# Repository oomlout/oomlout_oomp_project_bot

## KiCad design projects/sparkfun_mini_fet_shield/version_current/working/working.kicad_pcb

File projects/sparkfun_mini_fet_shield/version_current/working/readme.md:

# OOMP Project  
## Mini_FET_Shield  by sparkfun  
  
oomp key: oomp_projects_flat_sparkfun_mini_fet_shield  
(snippet of original readme)  
  
SparkFun Mini FET Shield  
========================================  

[*SparkFun Mini FET Shield (DEV-09627)*](https://www.sparkfun.com/products/9627)  
  
 Developed by Dave Vondle and IDEO Labs, this board is essentially the same as our Power Driver Shield, but the through-hole parts have been switched out for smaller SMD construction, allowing you to to drive high-current switches with your Arduino Pro Mini.   
 This is a great shield for small prototyping.  
  
 Repository Contents  
-------------------  
  
* **/Hardware** - Eagle design files (.brd, .sch)  
* **/Production** - Production panel files (.brd)  
  
Documentation  
--------------  
* **[Hookup Guide](https://learn.sparkfun.com/tutorials/mini-fet-shield-hookup-guide)** - Basic hookup guide for the Mini FET shield.  
* **[SparkFun Fritzing repo](https://github.com/sparkfun/Fritzing_Parts)** - Fritzing diagrams for SparkFun products.  
* **[SparkFun 3D Model repo](https://github.com/sparkfun/3D_Models)** - 3D models of SparkFun products.   

License Information  
-------------------  
This product is _**open source**_!   
  
The **hardware** is released under [Creative Commons ShareAlike 4.0 International](https://creativecommons.org/licenses/by-sa/4.0/).  
  
Please use, reuse, and modify these files as you see fit. Please maintain attribution to SparkFun Electronics and release anything derivative under the same license.  
  
Distributed as-is; no warranty is given.  
  
-   
  full source readme at [readme_src.md](readme_src.md)  
  
source repo at: [https://github.com/sparkfun/Mini_FET_Shield](https://github.com/sparkfun/Mini_FET_Shield)  
## Board  

## Schematic  

[schematic pdf](working_schematic.pdf)  
## Images

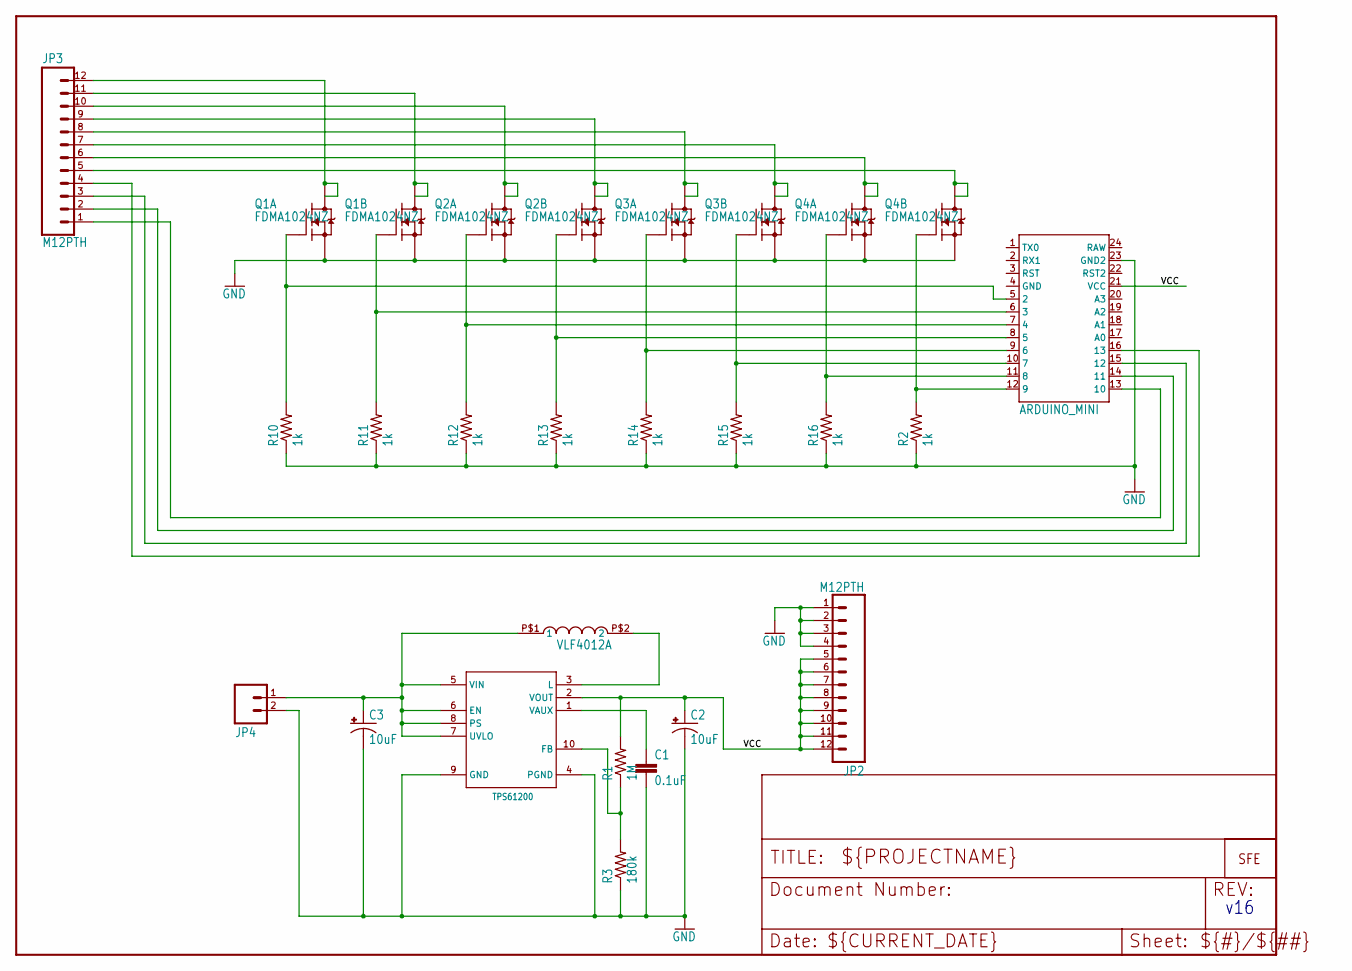
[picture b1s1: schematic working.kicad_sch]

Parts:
C1: 0.1uF; 0402-CAP
C2, C3: 10uF; EIA3216
JP2, JP3: M12PTH; 1X12
JP4: M02PTH; 1X02
JP5: LOGO-SFESK; SFE-LOGO-FLAME
Q1, Q2, Q3, Q4: FDMA1024NZ; MICROFET_2X2
R1: 1M; 0402-RES
R2, R10, R11, R12, R13, R14, R15, R16: 1k; 0402-RES
R3: 180k; 0402-RES
U1: TPS61200; DRC-S-PVSON-N10
U2: ARDUINO_MINI
UNK2.2UH0: VLF4012A

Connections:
GND: C1.2, C2.C (-), C3.C (-), JP2.1, JP2.2, JP2.3, JP2.4, JP4.2, Q1.S1 (S), Q1.S2 (S), Q2.S1 (S), Q2.S2 (S), Q3.S1 (S), Q3.S2 (S), Q4.S1 (S), Q4.S2 (S), R2.1, R3.1, R10.1, R11.1, R12.1, R13.1, R14.1, R15.1, R16.1, U1.4 (PGND), U1.9 (GND), U2.23 (GND2)
unnamed: JP3.4, U2.16 (13)
unnamed: R1.1, R3.2, U1.10 (FB)
unnamed: C1.1, U1.1 (VAUX)
unnamed: U1.3 (L), UNK2.2UH0.P$2 (2)
unnamed: Q1.G1 (G), R10.2, U2.5 (2)
unnamed: C3.A (+), JP4.1, U1.5 (VIN), U1.6 (EN), U1.7 (UVLO), U1.8 (PS), UNK2.2UH0.P$1 (1)
unnamed: Q1.G2 (G), R11.2, U2.6 (3)
unnamed: Q2.G1 (G), R12.2, U2.7 (4)
unnamed: Q2.G2 (G), R13.2, U2.8 (5)
unnamed: Q3.G1 (G), R14.2, U2.9 (6)
unnamed: Q3.G2 (G), R15.2, U2.10 (7)
unnamed: Q4.G1 (G), R16.2, U2.11 (8)
unnamed: Q4.G2 (G), R2.2, U2.12 (9)
unnamed: JP3.12, Q1.D1 (D), Q1.D1_2 (D1)
unnamed: JP3.11, Q1.D2 (D), Q1.D2_2 (D1)
unnamed: JP3.10, Q2.D1 (D), Q2.D1_2 (D1)
unnamed: JP3.9, Q2.D2 (D), Q2.D2_2 (D1)
unnamed: JP3.8, Q3.D1 (D), Q3.D1_2 (D1)
unnamed: JP3.7, Q3.D2 (D), Q3.D2_2 (D1)
unnamed: JP3.6, Q4.D1 (D), Q4.D1_2 (D1)
unnamed: JP3.5, Q4.D2 (D), Q4.D2_2 (D1)
unnamed: JP3.3, U2.15 (12)
unnamed: JP3.2, U2.14 (11)
unnamed: JP3.1, U2.13 (10)
VCC: C2.A (+), JP2.5, JP2.6, JP2.7, JP2.8, JP2.9, JP2.10, JP2.11, JP2.12, R1.2, U1.2 (VOUT), U2.21 (VCC)

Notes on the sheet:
v16

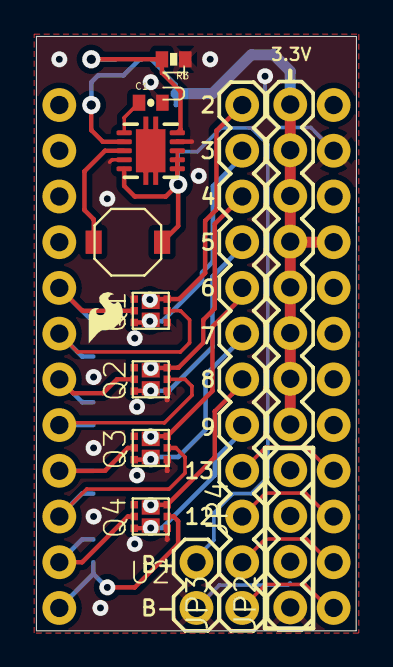
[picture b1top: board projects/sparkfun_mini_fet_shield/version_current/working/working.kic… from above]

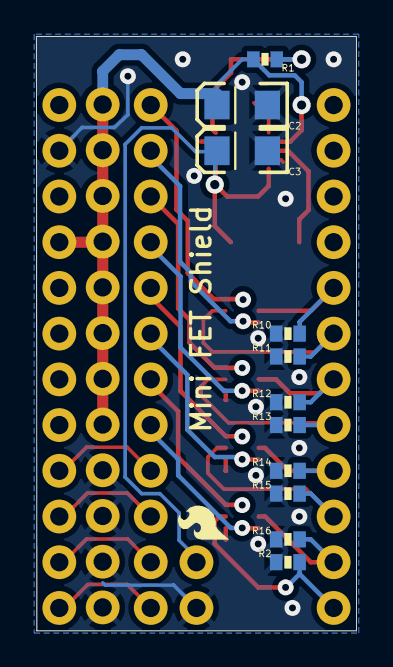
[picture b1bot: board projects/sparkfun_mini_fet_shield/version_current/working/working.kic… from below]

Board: 2 copper layers, 17.8 x 33.0 mm, 25 parts (12 on the bottom side), 26 nets.

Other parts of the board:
JP1: LOGO-SFESK; SFE-LOGO-FLAME

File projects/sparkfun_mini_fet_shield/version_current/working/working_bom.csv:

"Id";"Designator";"Footprint";"Quantity";"Designation";"Supplier and ref";
1;"JP2,JP3";"1X12";2;"M12PTH";;;
2;"R3";"0402-RES";1;"180k";;;
3;"U2";"ARDUINO_MINI";1;"ARDUINO_MINI";;;
4;"C1";"0402-CAP";1;"0.1uF";;;
5;"JP4";"1X02";1;"";;;
6;"UNK2.2UH0";"VLF4012A";1;"2.2uH";;;
7;"Q3,Q2,Q1,Q4";"MICROFET_2X2";4;"FDMA1024NZ";;;
8;"U1";"DRC-S-PVSON-N10";1;"TPS61200";;;
9;"JP1,JP5";"SFE-LOGO-FLAME";2;"LOGO-SFESK";;;
10;"R15,R14,R10,R2,R12,R11,R16,R13";"0402-RES";8;"1k";;;
11;"R1";"0402-RES";1;"1M";;;
12;"C2,C3";"EIA3216";2;"10uF";;;

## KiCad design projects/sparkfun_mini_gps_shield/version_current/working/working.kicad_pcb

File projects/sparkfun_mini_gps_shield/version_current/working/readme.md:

# OOMP Project  
## Mini_GPS_Shield  by sparkfun  
  
oomp key: oomp_projects_flat_sparkfun_mini_gps_shield  
(snippet of original readme)  
  
SparkFun Mini GPS Shield  
=============================================  

[*SparkFun Mini GPS Shield (GPS-14030)*](https://www.sparkfun.com/products/14030)  
  
The [SparkFun Mini GPS Shield](https://www.sparkfun.com/products/14030) equips your Arduino with access to a GPS module, µSD memory card socket, and all of the other peripherals you'll need to turn your Arduino into a position-tracking, speed-monitoring, altitude-observing wonder logger. The shield is based around the [GP-735](https://www.sparkfun.com/products/13670) GPS Module -- a 56-channel GPS receiver featuring a uBlox 7th generation chipset and an up to 10Hz update rate.  
   
 Repository Contents  
-------------------  
* **/Hardware** - All Eagle design files (.brd, .sch)  
  
Documentation  
-------------------  
* [**Hookup Guide**](https://learn.sparkfun.com/tutorials/wireless-joystick-hookup-guide)  

License Information  
-------------------  
The hardware is released under [Creative Commons ShareAlike 4.0 International](https://creativecommons.org/licenses/by-sa/4.0/).  
The code is beerware; if you see me (or any other SparkFun employee) at the local, and you've found our code helpful, please buy us a round!  
  full source readme at [readme_src.md](readme_src.md)  
  
source repo at: [https://github.com/sparkfun/Mini_GPS_Shield](https://github.com/sparkfun/Mini_GPS_Shield)  
## Board  

## Schematic  

[schematic pdf](working_schematic.pdf)  
## Images

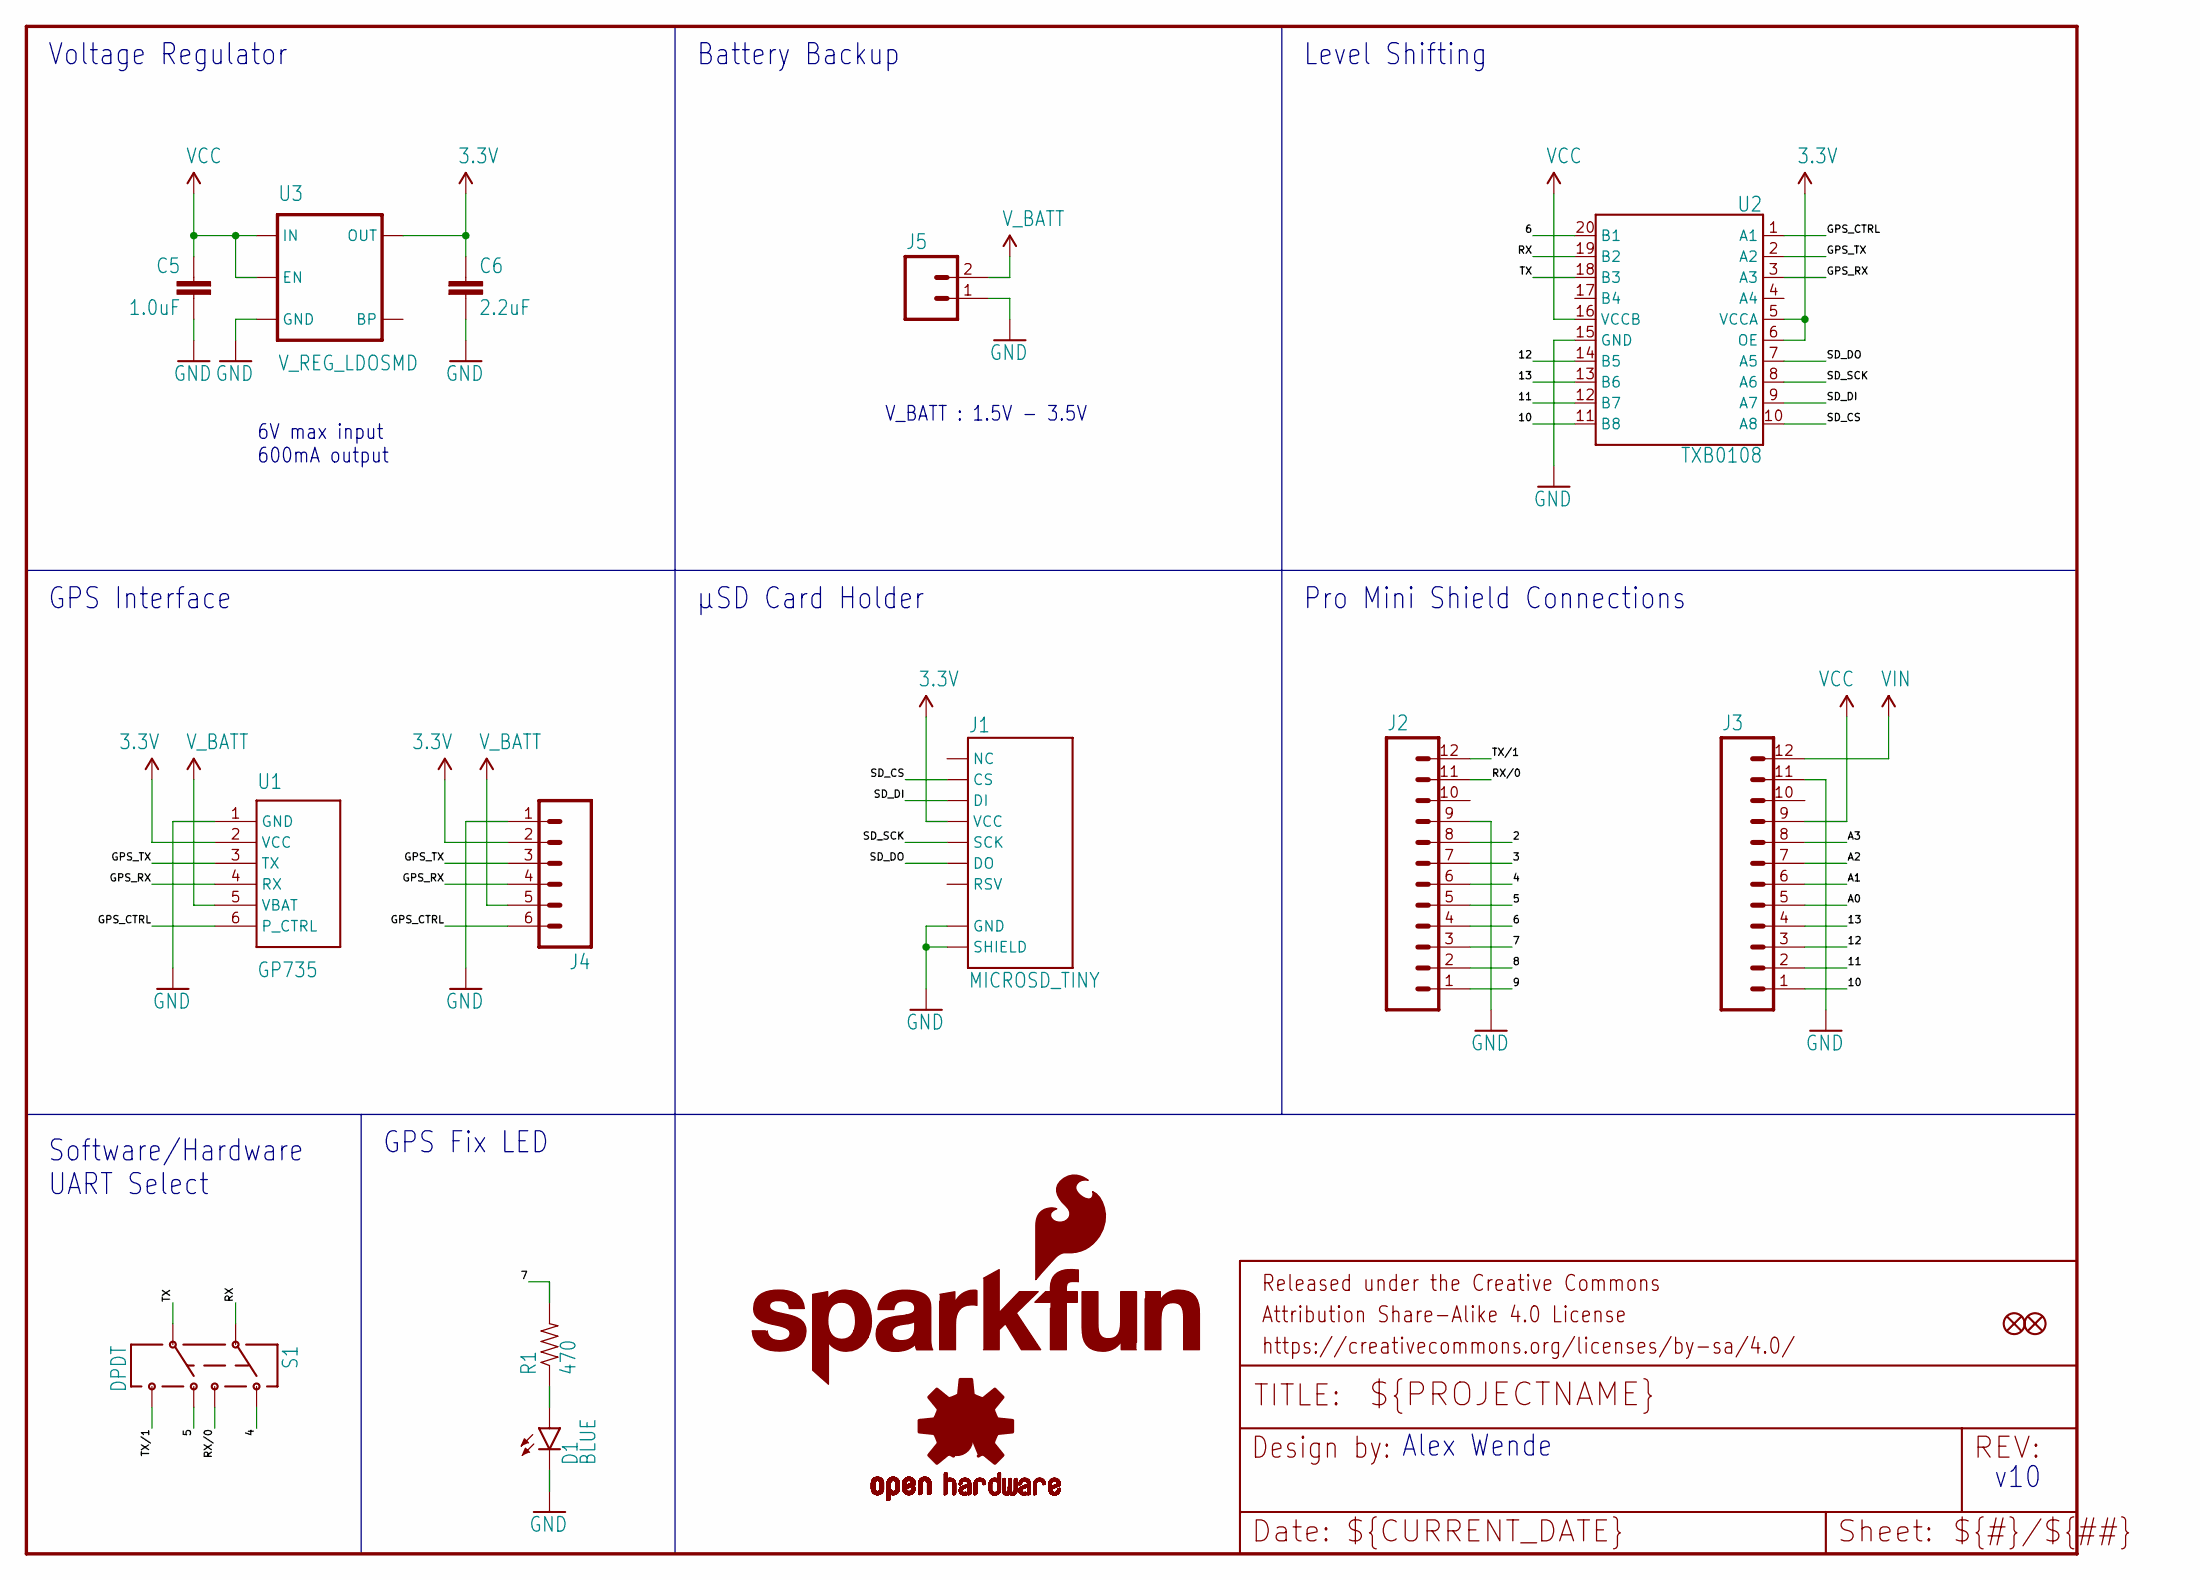
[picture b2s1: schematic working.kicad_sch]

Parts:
C5: 1.0uF; 0805-CAP
C6: 2.2uF; 0603-CAP
D1: BLUE; LED-0603
FD1, FD2: FIDUCIALUFIDUCIAL; MICRO-FIDUCIAL
FRAME1: FRAME-LETTER; CREATIVE_COMMONS
J1: MICROSD_TINY
J2, J3: M12NO_SILK; 1X12_NO_SILK
J4: M06NO_SILK_FEMALE_PTH; 1X06_NO_SILK
J5: M021X02_NO_SILK; 1X02_NO_SILK
LOGO1: OSHW-LOGOS; OSHW-LOGO-S
LOGO3: SFE_LOGO_FLAME.1_INCH; SFE_LOGO_FLAME_.1
LOGO4: SFE_LOGO_NAME.1_INCH; SFE_LOGO_NAME_.1
R1: 470; 0603-RES
S1: DPDT; AYZ0202
U1: GP735
U2: TXB0108; UFDFN-20
U3: V_REG_LDOSMD; SOT23-5

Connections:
2: J2.8
3: J2.7
3.3V: C6.1, J1.4 (VCC), J4.2, U1.2 (VCC), U2.5 (VCCA), U2.6 (OE), U3.5 (OUT)
4: J2.6, S1.1
5: J2.5, S1.4
6: J2.4, U2.20 (B1)
7: J2.3, R1.2
8: J2.2
9: J2.1
10: J3.1, U2.11 (B8)
11: J3.2, U2.12 (B7)
12: J3.3, U2.14 (B5)
13: J3.4, U2.13 (B6)
A0: J3.5
A1: J3.6
A2: J3.7
A3: J3.8
GND: C5.2, C6.2, D1.C, J1.6 (GND), J1.GND1 (SHIELD), J1.GND2 (SHIELD), J1.GND3 (SHIELD), J1.GND4 (SHIELD), J1.GND5 (SHIELD), J1.GND6 (SHIELD), J2.9, J3.11, J4.1, J5.1, U1.1 (GND), U2.15 (GND), U3.2 (GND)
GPS_CTRL: J4.6, U1.6 (P_CTRL), U2.1 (A1)
GPS_RX: J4.4, U1.4 (RX), U2.3 (A3)
GPS_TX: J4.3, U1.3 (TX), U2.2 (A2)
unnamed: D1.A, R1.1
RX: S1.2, U2.19 (B2)
RX/0: J2.11, S1.3
SD_CS: J1.2 (CS), U2.10 (A8)
SD_DI: J1.3 (DI), U2.9 (A7)
SD_DO: J1.7 (DO), U2.7 (A5)
SD_SCK: J1.5 (SCK), U2.8 (A6)
TX: S1.5, U2.18 (B3)
TX/1: J2.12, S1.6
VCC: C5.1, J3.9, U2.16 (VCCB), U3.1 (IN), U3.3 (EN)
VIN: J3.12
V_BATT: J4.5, J5.2, U1.5 (VBAT)

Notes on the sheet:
GPS Fix LED
Pro Mini Shield Connections
GPS Interface
Battery Backup
v10
Voltage Regulator
Level Shifting
μSD Card Holder
V_BATT : 1.5V - 3.5V
Software/Hardware UART Select
Alex Wende
6V max input 600mA output

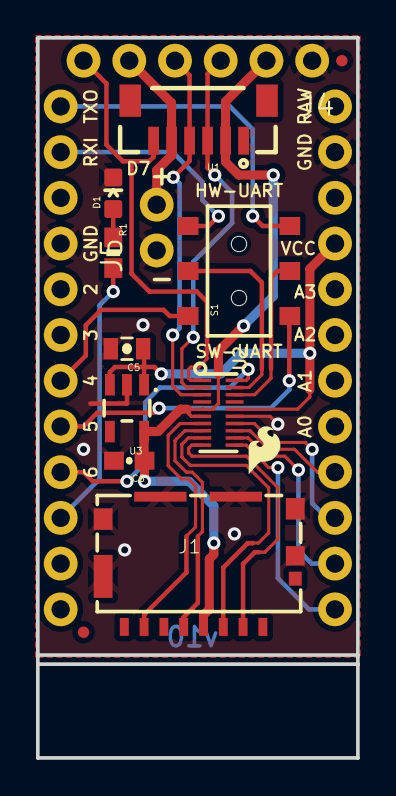
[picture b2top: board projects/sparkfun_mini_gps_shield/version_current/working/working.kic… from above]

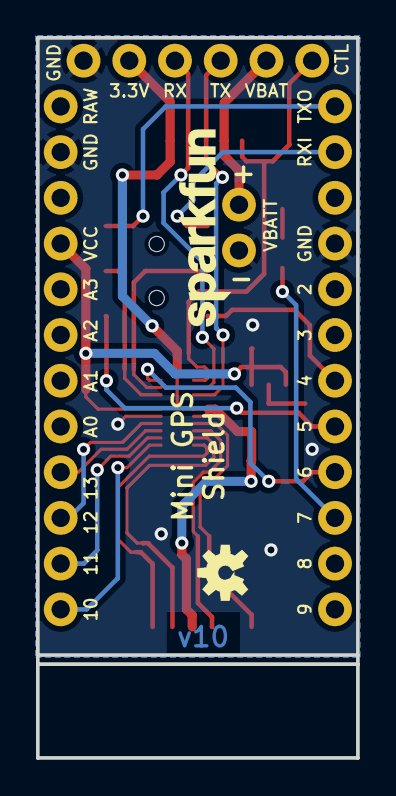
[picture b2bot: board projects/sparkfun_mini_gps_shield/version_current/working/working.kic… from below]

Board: 2 copper layers, 17.8 x 40.0 mm, 19 parts (2 on the bottom side), 24 nets.

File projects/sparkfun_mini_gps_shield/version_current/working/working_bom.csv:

Row,Description,Part,References,Value,Footprint,Quantity Per PCB,Status,Datasheet,PROD_ID
1,,1.0UF-25V-+80/-20(0805){dblquote},C5,1.0uF,0805-CAP,1, ,,
2,,2.2UF-10V-20%(0603),C6,2.2uF,0603-CAP,1, ,,
3,,LED-BLUE0603,D1,BLUE,LED-0603,1, ,,
4,,FRAME-LETTER,FRAME1,FRAME-LETTER,CREATIVE_COMMONS,1, ,,
5,,M021X02_NO_SILK,J5,M021X02_NO_SILK,1X02_NO_SILK,1, ,,
6,,M06NO_SILK_FEMALE_PTH,J4,M06NO_SILK_FEMALE_PTH,1X06_NO_SILK,1, ,,
7,,M12NO_SILK,J2 J3,M12NO_SILK,1X12_NO_SILK,2, ,,
8,,MICROSD_TINY,J1,MICROSD_TINY,MICROSD_TINY,1, ,,
9,,OSHW-LOGOS,LOGO1,OSHW-LOGOS,OSHW-LOGO-S,1, ,,
10,,SFE_LOGO_FLAME.1_INCH,LOGO3,SFE_LOGO_FLAME.1_INCH,SFE_LOGO_FLAME_.1,1, ,,
11,,SFE_LOGO_NAME.1_INCH,LOGO4,SFE_LOGO_NAME.1_INCH,SFE_LOGO_NAME_.1,1, ,,
12,,470OHM1/10W1%(0603),R1,470,0603-RES,1, ,,
13,,SWITCH-DPDTAYZ0202,S1,DPDT,AYZ0202,1, ,,
14,,GP735,U1,GP735,GP735,1, ,,
15,,TXB0108,U2,TXB0108,UFDFN-20,1, ,,
16,,V_REG_LDOSMD,U3,V_REG_LDOSMD,SOT23-5,1, ,,VREG-12457





Project info:
Schematic:,working
Variant:,default
Revision:,
Date:,2023-08-06_12-56-08
KiCad Version:,7.0.6-7.0.6~ubuntu22.04.1
Statistics:
Component Groups:,16
Component Count:,17 (0 SMD/ 0 THT)
Fitted Components:,17 (0 SMD/ 0 THT)
Number of PCBs:,1
Total Components:,17

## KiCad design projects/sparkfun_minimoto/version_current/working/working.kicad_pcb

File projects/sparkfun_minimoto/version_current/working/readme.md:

# OOMP Project  
## MiniMoto  by sparkfun  
  
oomp key: oomp_projects_flat_sparkfun_minimoto  
(snippet of original readme)  
  
**NOTE:** *This product has been retired from our catalog. If you are looking for more up-to-date info, please check out some of these resources to see how other users are still hacking and improving on this product.*  
* *[SparkFun Forum](https://forum.sparkfun.com/)*  
* *[Comments Here on GitHub](https://github.com/sparkfun/MiniMoto/issues)*  
* *[IRC Channel](https://www.sparkfun.com/news/263)*  
  
SparkFun MiniMoto Breakout - DRV8830  
=========================================  

[*SparkFun MiniMoto Breakout - DRV8830(BOB-11890)*](https://www.sparkfun.com/products/11890)  
  
The MiniMoto is a breakout board for the DRV8830 I<sup>2</sup>C DC motor driver. It operates between 2.7V to 6.8V  
  
Repository Contents  
-------------------  
* **/Hardware** - All Eagle design files (.brd, .sch)  
* **/Libraries** - All Arduino libraries and board examples  
* **/Production** - Test bed files and production panel files  
  
Documentation  
--------------  
* **[Library](https://github.com/sparkfun/SparkFun_MiniMoto_Arduino_Library)** - Arduinolibrary for the MiniMoto.  
* **[Hookup Guide](https://learn.sparkfun.com/tutorials/minimoto-drv8830-hookup-guide)** - Basic hookup guide for the MiniMoto.  
* **[SparkFun Fritzing repo](https://github.com/sparkfun/Fritzing_Parts)** - Fritzing diagrams for SparkFun products.  
* **[SparkFun 3D Model repo](https://github.com/sparkfun/3D_Models)** - 3D models o  
  full source readme at [readme_src.md](readme_src.md)  
  
source repo at: [https://github.com/sparkfun/MiniMoto](https://github.com/sparkfun/MiniMoto)  
## Board  

## Schematic  

[schematic pdf](working_schematic.pdf)  
## Images

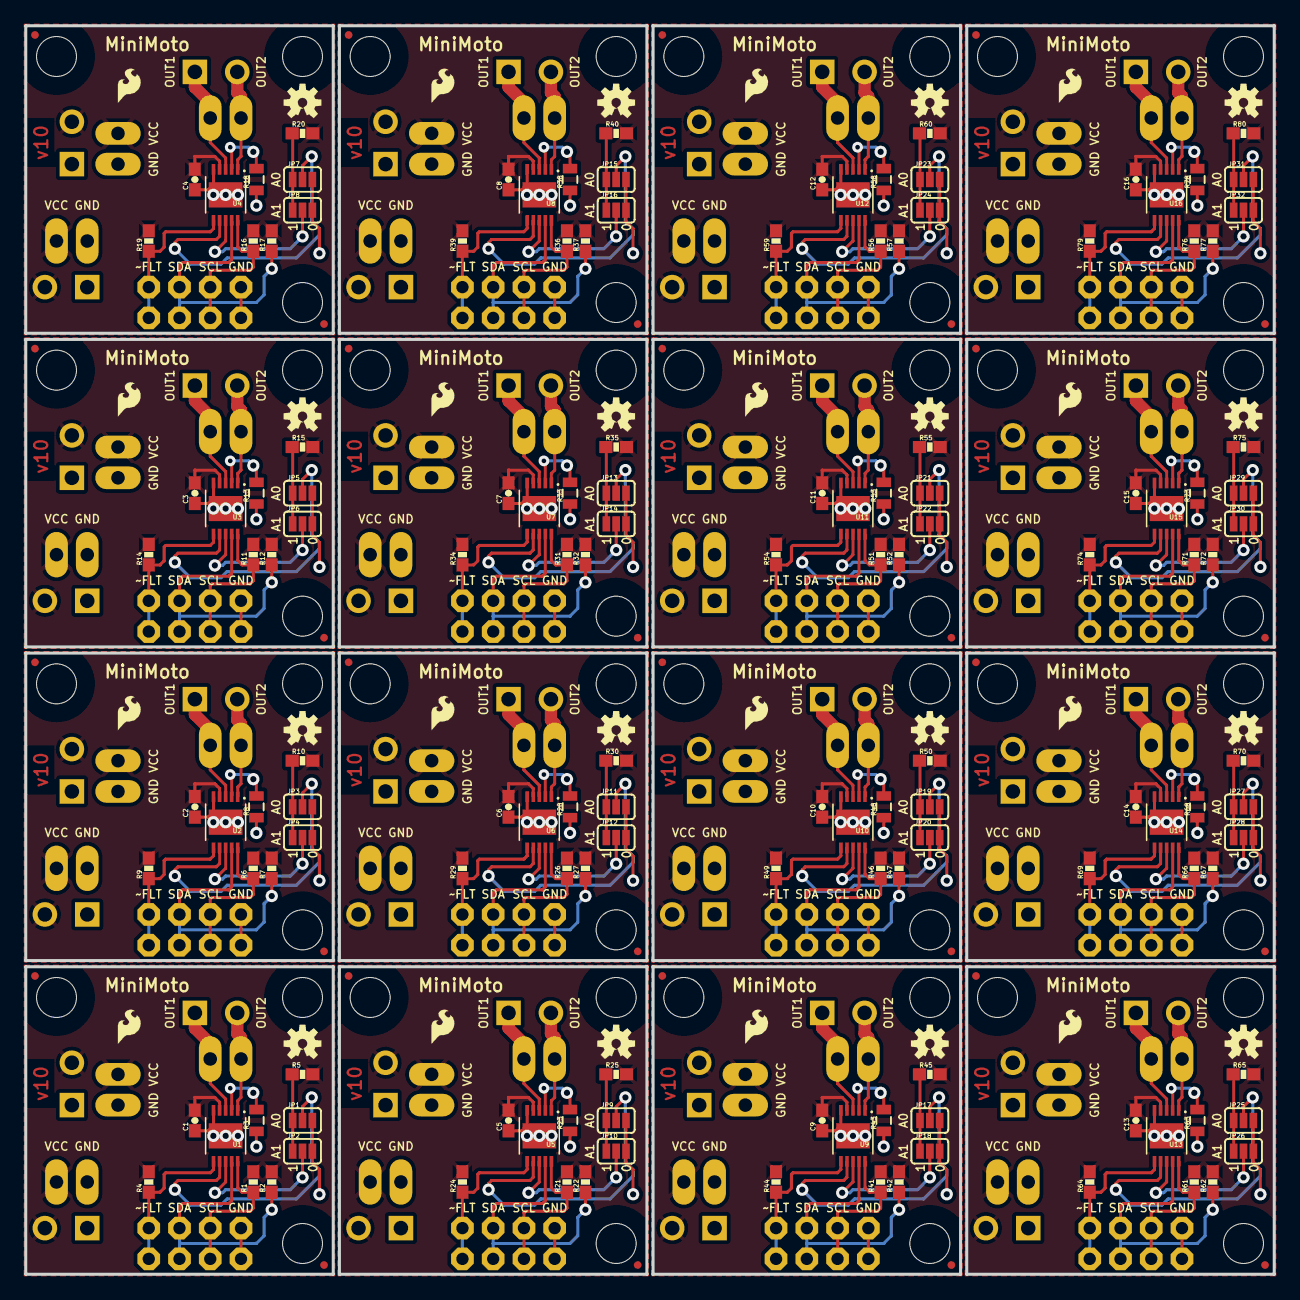
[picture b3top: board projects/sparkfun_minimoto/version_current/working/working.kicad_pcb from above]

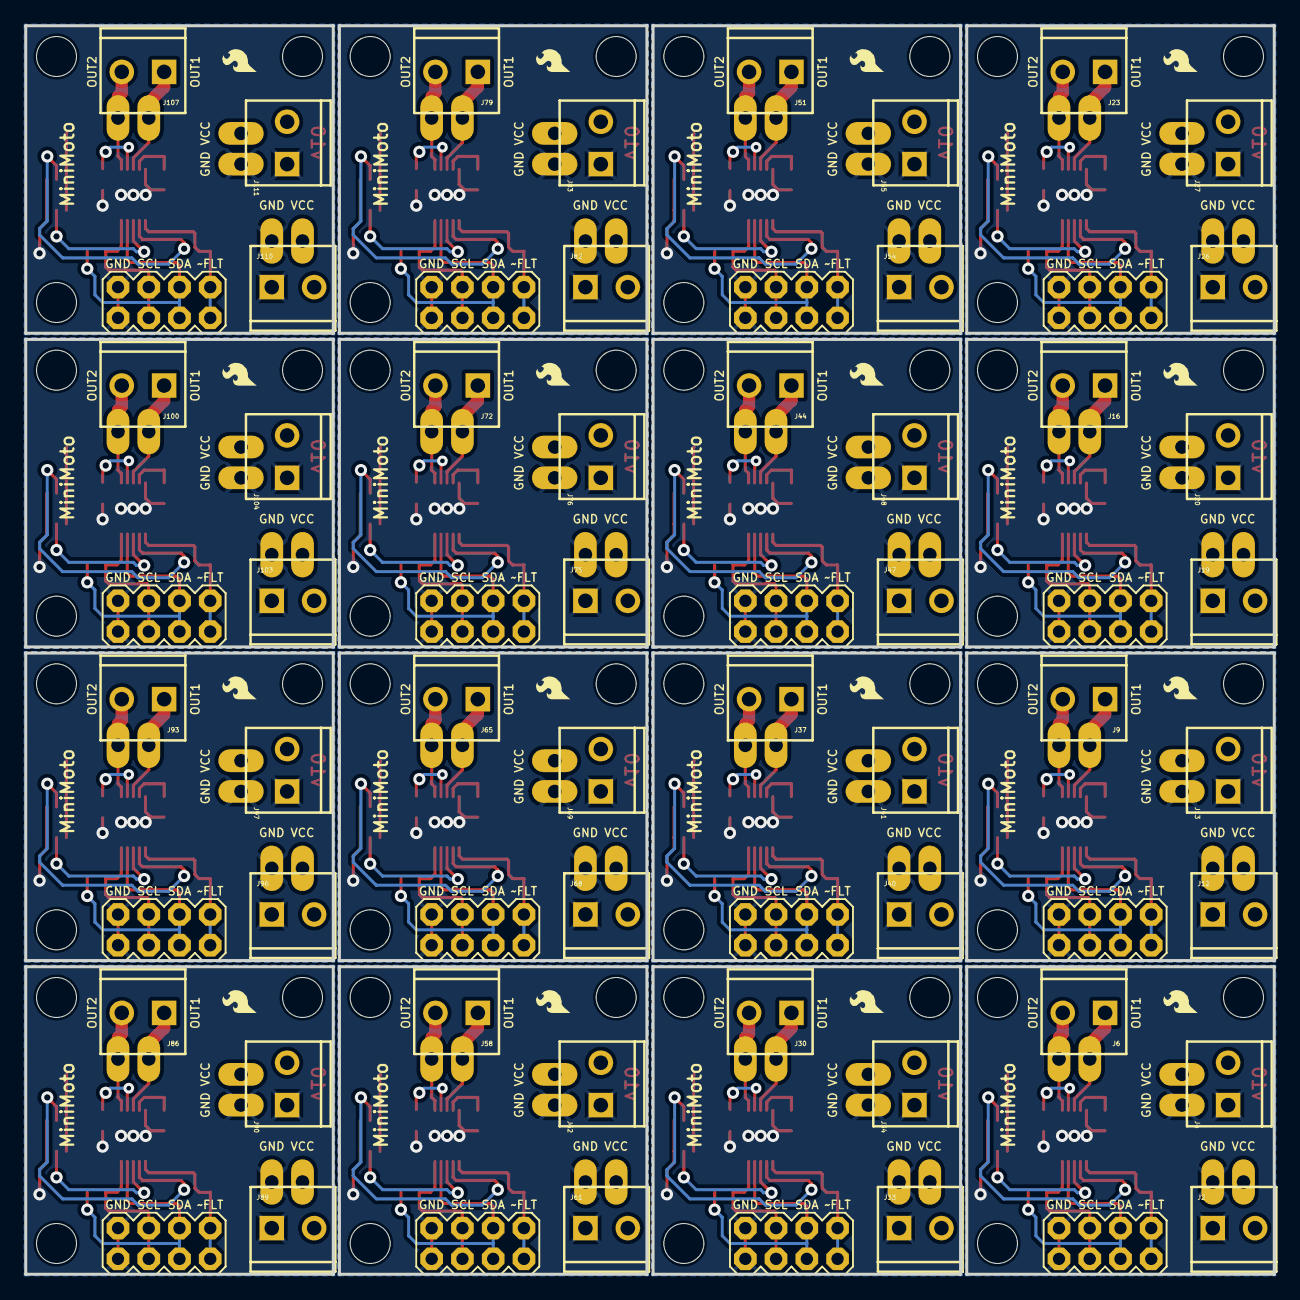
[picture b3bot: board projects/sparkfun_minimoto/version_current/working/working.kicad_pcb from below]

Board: 4 copper layers, 103.1 x 103.1 mm, 384 parts (112 on the bottom side), 176 nets.

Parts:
C1, C2, C3, C4, C5, C6, C7, C8, C9, C10, C11, C12, C13, C14, C15, C16: 0.1uF; 0603-CAP
FID1, FID2, FID3, FID4, FID5, FID6, FID7, FID8, FID9, FID10, FID11, FID12, FID13, FID14, FID15, FID16, FID17, FID18, FID19, FID20, FID21, FID22, FID23, FID24, FID25, FID26, FID27, FID28, FID29, FID30, FID31, FID32: FIDUCIALUFIDUCIAL; MICRO-FIDUCIAL
J1, J3, J5, J8, J11, J14, J15, J18, J21, J22, J25, J28, J29, J32, J35, J36, J39, J42, J43, J46, J49, J50, J53, J56, J57, J60, J63, J64, J67, J70, J71, J74, J77, J78, J81, J84, J85, J88, J91, J92, J95, J98, J99, J102, J105, J106, J109, J112: M02PTH3; 1X02_LONGPADS
J2, J4, J6, J9, J12, J13, J16, J19, J20, J23, J26, J27, J30, J33, J34, J37, J40, J41, J44, J47, J48, J51, J54, J55, J58, J61, J62, J65, J68, J69, J72, J75, J76, J79, J82, J83, J86, J89, J90, J93, J96, J97, J100, J103, J104, J107, J110, J111: M023.5MM; SCREWTERMINAL-3.5MM-2
J7, J10, J17, J24, J31, J38, J45, J52, J59, J66, J73, J80, J87, J94, J101, J108: M04X2; 2X4
JP1, JP2, JP3, JP4, JP5, JP6, JP7, JP8, JP9, JP10, JP11, JP12, JP13, JP14, JP15, JP16, JP17, JP18, JP19, JP20, JP21, JP22, JP23, JP24, JP25, JP26, JP27, JP28, JP29, JP30, JP31, JP32: JUMPER-31-2; SJ_3_PASTE1&2
LOGO1, LOGO3, LOGO5, LOGO6, LOGO8, LOGO9, LOGO11, LOGO12, LOGO14, LOGO15, LOGO17, LOGO18, LOGO20, LOGO21, LOGO23, LOGO24, LOGO26, LOGO27, LOGO29, LOGO30, LOGO32, LOGO33, LOGO35, LOGO36, LOGO38, LOGO39, LOGO41, LOGO42, LOGO44, LOGO45, LOGO47, LOGO48: LOGO-SFESK; SFE-LOGO-FLAME
LOGO2, LOGO4, LOGO7, LOGO10, LOGO13, LOGO16, LOGO19, LOGO22, LOGO25, LOGO28, LOGO31, LOGO34, LOGO37, LOGO40, LOGO43, LOGO46: OSHW-LOGOS; OSHW-LOGO-S
R1, R2, R6, R7, R11, R12, R16, R17, R21, R22, R26, R27, R31, R32, R36, R37, R41, R42, R46, R47, R51, R52, R56, R57, R61, R62, R66, R67, R71, R72, R76, R77: 1K; 0603-RES
R3, R8, R13, R18, R23, R28, R33, R38, R43, R48, R53, R58, R63, R68, R73, R78: 0.22; 0805
R4, R5, R9, R10, R14, R15, R19, R20, R24, R25, R29, R30, R34, R35, R39, R40, R44, R45, R49, R50, R54, R55, R59, R60, R64, R65, R69, R70, R74, R75, R79, R80: 10K; 0603-RES
STANDOFF1, STANDOFF2, STANDOFF3, STANDOFF4, STANDOFF5, STANDOFF6, STANDOFF7, STANDOFF8, STANDOFF9, STANDOFF10, STANDOFF11, STANDOFF12, STANDOFF13, STANDOFF14, STANDOFF15, STANDOFF16, STANDOFF17, STANDOFF18, STANDOFF19, STANDOFF20, STANDOFF21, STANDOFF22, STANDOFF23, STANDOFF24, STANDOFF25, STANDOFF26, STANDOFF27, STANDOFF28, STANDOFF29, STANDOFF30, STANDOFF31, STANDOFF32, STANDOFF33, STANDOFF34, STANDOFF35, STANDOFF36, STANDOFF37, STANDOFF38, STANDOFF39, STANDOFF40, STANDOFF41, STANDOFF42, STANDOFF43, STANDOFF44, STANDOFF45, STANDOFF46, STANDOFF47, STANDOFF48: STAND-OFF
U1, U2, U3, U4, U5, U6, U7, U8, U9, U10, U11, U12, U13, U14, U15, U16: DRV8830; MSOP-10-GNDPAD

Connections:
A0: JP1.2, U1.7
A1: JP2.2, U1.8
A2: JP3.2, U2.7
A3: JP4.2, U2.8
A4: JP5.2, U3.7
A5: JP6.2, U3.8
A6: JP7.2, U4.7
A7: JP8.2, U4.8
A8: JP9.2, U5.7
A9: JP10.2, U5.8
A10: JP11.2, U6.7
A11: JP12.2, U6.8
A12: JP13.2, U7.7
A13: JP14.2, U7.8
A14: JP15.2, U8.7
A15: JP16.2, U8.8
A16: JP17.2, U9.7
A17: JP18.2, U9.8
A18: JP19.2, U10.7
A19: JP20.2, U10.8
A20: JP21.2, U11.7
A21: JP22.2, U11.8
A22: JP23.2, U12.7
A23: JP24.2, U12.8
A24: JP25.2, U13.7
A25: JP26.2, U13.8
A26: JP27.2, U14.7
A27: JP28.2, U14.8
A28: JP29.2, U15.7
A29: JP30.2, U15.8
A30: JP31.2, U16.7
A31: JP32.2, U16.8
GND: C1.1, J1.1, J2.1, J3.1, J4.1, J7.7, J7.8, JP1.3, JP2.3, R3.1, U1.5, U1.GND
GND1: C2.1, J10.7, J10.8, J11.1, J12.1, J13.1, J14.1, JP3.3, JP4.3, R8.1, U2.5, U2.GND
GND2: C3.1, J17.7, J17.8, J18.1, J19.1, J20.1, J21.1, JP5.3, JP6.3, R13.1, U3.5, U3.GND
GND3: C4.1, J24.7, J24.8, J25.1, J26.1, J27.1, J28.1, JP7.3, JP8.3, R18.1, U4.5, U4.GND
GND4: C5.1, J31.7, J31.8, J32.1, J33.1, J34.1, J35.1, JP9.3, JP10.3, R23.1, U5.5, U5.GND
GND5: C6.1, J38.7, J38.8, J39.1, J40.1, J41.1, J42.1, JP11.3, JP12.3, R28.1, U6.5, U6.GND
GND6: C7.1, J45.7, J45.8, J46.1, J47.1, J48.1, J49.1, JP13.3, JP14.3, R33.1, U7.5, U7.GND
GND7: C8.1, J52.7, J52.8, J53.1, J54.1, J55.1, J56.1, JP15.3, JP16.3, R38.1, U8.5, U8.GND
GND8: C9.1, J59.7, J59.8, J60.1, J61.1, J62.1, J63.1, JP17.3, JP18.3, R43.1, U9.5, U9.GND
GND9: C10.1, J66.7, J66.8, J67.1, J68.1, J69.1, J70.1, JP19.3, JP20.3, R48.1, U10.5, U10.GND
GND10: C11.1, J73.7, J73.8, J74.1, J75.1, J76.1, J77.1, JP21.3, JP22.3, R53.1, U11.5, U11.GND
GND11: C12.1, J80.7, J80.8, J81.1, J82.1, J83.1, J84.1, JP23.3, JP24.3, R58.1, U12.5, U12.GND
GND12: C13.1, J87.7, J87.8, J88.1, J89.1, J90.1, J91.1, JP25.3, JP26.3, R63.1, U13.5, U13.GND
GND13: C14.1, J94.7, J94.8, J95.1, J96.1, J97.1, J98.1, JP27.3, JP28.3, R68.1, U14.5, U14.GND
GND14: C15.1, J101.7, J101.8, J102.1, J103.1, J104.1, J105.1, JP29.3, JP30.3, R73.1, U15.5, U15.GND
GND15: C16.1, J108.7, J108.8, J109.1, J110.1, J111.1, J112.1, JP31.3, JP32.3, R78.1, U16.5, U16.GND
unnamed: JP1.1, JP2.1, R5.1
unnamed: R8.2, U2.2
unnamed: R3.2, U1.2
unnamed: JP3.1, JP4.1, R10.1
unnamed: R13.2, U3.2
unnamed: JP5.1, JP6.1, R15.1
unnamed: R18.2, U4.2
unnamed: JP7.1, JP8.1, R20.1
unnamed: R23.2, U5.2
unnamed: JP9.1, JP10.1, R25.1
unnamed: R28.2, U6.2
unnamed: JP11.1, JP12.1, R30.1
unnamed: R33.2, U7.2
unnamed: JP13.1, JP14.1, R35.1
unnamed: R38.2, U8.2
unnamed: JP15.1, JP16.1, R40.1
unnamed: R43.2, U9.2
unnamed: JP17.1, JP18.1, R45.1
unnamed: R48.2, U10.2
unnamed: JP19.1, JP20.1, R50.1
unnamed: R53.2, U11.2
unnamed: JP21.1, JP22.1, R55.1
unnamed: R58.2, U12.2
unnamed: JP23.1, JP24.1, R60.1
unnamed: R63.2, U13.2
unnamed: JP25.1, JP26.1, R65.1
unnamed: R68.2, U14.2
unnamed: JP27.1, JP28.1, R70.1
unnamed: R73.2, U15.2
unnamed: JP29.1, JP30.1, R75.1
unnamed: R78.2, U16.2
unnamed: JP31.1, JP32.1, R80.1
OUT1: J5.1, J6.1, U1.3
OUT2: J5.2, J6.2, U1.1
OUT3: J8.1, J9.1, U2.3
OUT4: J8.2, J9.2, U2.1
OUT5: J15.1, J16.1, U3.3
OUT6: J15.2, J16.2, U3.1
OUT7: J22.1, J23.1, U4.3
OUT8: J22.2, J23.2, U4.1
OUT9: J29.1, J30.1, U5.3
OUT10: J29.2, J30.2, U5.1
OUT11: J36.1, J37.1, U6.3
OUT12: J36.2, J37.2, U6.1
OUT13: J43.1, J44.1, U7.3
OUT14: J43.2, J44.2, U7.1
OUT15: J50.1, J51.1, U8.3
OUT16: J50.2, J51.2, U8.1
OUT17: J57.1, J58.1, U9.3
OUT18: J57.2, J58.2, U9.1
OUT19: J64.1, J65.1, U10.3
OUT20: J64.2, J65.2, U10.1
OUT21: J71.1, J72.1, U11.3
OUT22: J71.2, J72.2, U11.1
OUT23: J78.1, J79.1, U12.3
OUT24: J78.2, J79.2, U12.1
OUT25: J85.1, J86.1, U13.3
OUT26: J85.2, J86.2, U13.1
OUT27: J92.1, J93.1, U14.3
OUT28: J92.2, J93.2, U14.1
OUT29: J99.1, J100.1, U15.3
OUT30: J99.2, J100.2, U15.1
OUT31: J106.1, J107.1, U16.3
OUT32: J106.2, J107.2, U16.1
SCL: J7.5, J7.6, R1.1, U1.10
SCL1: J10.5, J10.6, R6.1, U2.10
SCL2: J17.5, J17.6, R11.1, U3.10
SCL3: J24.5, J24.6, R16.1, U4.10
SCL4: J31.5, J31.6, R21.1, U5.10
SCL5: J38.5, J38.6, R26.1, U6.10
SCL6: J45.5, J45.6, R31.1, U7.10
SCL7: J52.5, J52.6, R36.1, U8.10
SCL8: J59.5, J59.6, R41.1, U9.10
SCL9: J66.5, J66.6, R46.1, U10.10
SCL10: J73.5, J73.6, R51.1, U11.10
SCL11: J80.5, J80.6, R56.1, U12.10
SCL12: J87.5, J87.6, R61.1, U13.10
SCL13: J94.5, J94.6, R66.1, U14.10
SCL14: J101.5, J101.6, R71.1, U15.10
SCL15: J108.5, J108.6, R76.1, U16.10
SDA: J7.3, J7.4, R2.1, U1.9
SDA1: J10.3, J10.4, R7.1, U2.9
SDA2: J17.3, J17.4, R12.1, U3.9
SDA3: J24.3, J24.4, R17.1, U4.9
SDA4: J31.3, J31.4, R22.1, U5.9
SDA5: J38.3, J38.4, R27.1, U6.9
SDA6: J45.3, J45.4, R32.1, U7.9
SDA7: J52.3, J52.4, R37.1, U8.9
SDA8: J59.3, J59.4, R42.1, U9.9
SDA9: J66.3, J66.4, R47.1, U10.9
SDA10: J73.3, J73.4, R52.1, U11.9
SDA11: J80.3, J80.4, R57.1, U12.9
SDA12: J87.3, J87.4, R62.1, U13.9
SDA13: J94.3, J94.4, R67.1, U14.9
SDA14: J101.3, J101.4, R72.1, U15.9
SDA15: J108.3, J108.4, R77.1, U16.9
VCC: C1.2, J1.2, J2.2, J3.2, J4.2, R1.2, R2.2, R4.2, R5.2, U1.4
VCC1: C2.2, J11.2, J12.2, J13.2, J14.2, R6.2, R7.2, R9.2, R10.2, U2.4
VCC2: C3.2, J18.2, J19.2, J20.2, J21.2, R11.2, R12.2, R14.2, R15.2, U3.4
VCC3: C4.2, J25.2, J26.2, J27.2, J28.2, R16.2, R17.2, R19.2, R20.2, U4.4
VCC4: C5.2, J32.2, J33.2, J34.2, J35.2, R21.2, R22.2, R24.2, R25.2, U5.4
VCC5: C6.2, J39.2, J40.2, J41.2, J42.2, R26.2, R27.2, R29.2, R30.2, U6.4
VCC6: C7.2, J46.2, J47.2, J48.2, J49.2, R31.2, R32.2, R34.2, R35.2, U7.4
VCC7: C8.2, J53.2, J54.2, J55.2, J56.2, R36.2, R37.2, R39.2, R40.2, U8.4
VCC8: C9.2, J60.2, J61.2, J62.2, J63.2, R41.2, R42.2, R44.2, R45.2, U9.4
VCC9: C10.2, J67.2, J68.2, J69.2, J70.2, R46.2, R47.2, R49.2, R50.2, U10.4
VCC10: C11.2, J74.2, J75.2, J76.2, J77.2, R51.2, R52.2, R54.2, R55.2, U11.4
VCC11: C12.2, J81.2, J82.2, J83.2, J84.2, R56.2, R57.2, R59.2, R60.2, U12.4
VCC12: C13.2, J88.2, J89.2, J90.2, J91.2, R61.2, R62.2, R64.2, R65.2, U13.4
VCC13: C14.2, J95.2, J96.2, J97.2, J98.2, R66.2, R67.2, R69.2, R70.2, U14.4
VCC14: C15.2, J102.2, J103.2, J104.2, J105.2, R71.2, R72.2, R74.2, R75.2, U15.4
VCC15: C16.2, J109.2, J110.2, J111.2, J112.2, R76.2, R77.2, R79.2, R80.2, U16.4
~FAULT1: J10.1, J10.2, R9.1, U2.6
~FAULT2: J17.1, J17.2, R14.1, U3.6
~FAULT3: J24.1, J24.2, R19.1, U4.6
~FAULT4: J31.1, J31.2, R24.1, U5.6
~FAULT5: J38.1, J38.2, R29.1, U6.6
~FAULT6: J45.1, J45.2, R34.1, U7.6
~FAULT7: J52.1, J52.2, R39.1, U8.6
~FAULT8: J59.1, J59.2, R44.1, U9.6
~FAULT9: J66.1, J66.2, R49.1, U10.6
~FAULT10: J73.1, J73.2, R54.1, U11.6
~FAULT11: J80.1, J80.2, R59.1, U12.6
~FAULT12: J87.1, J87.2, R64.1, U13.6
~FAULT13: J94.1, J94.2, R69.1, U14.6
~FAULT14: J101.1, J101.2, R74.1, U15.6
~FAULT15: J108.1, J108.2, R79.1, U16.6
~FAULT: J7.1, J7.2, R4.1, U1.6

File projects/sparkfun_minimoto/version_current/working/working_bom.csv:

Row,Description,Part,References,Value,Footprint,Quantity Per PCB,Status,Datasheet
1,,0.1UF-25V(+80/-20%)(0603),C1,0.1uF,0603-CAP,1, ,
2,,FRAME-LETTER,FRAME1,FRAME-LETTER,CREATIVE_COMMONS,1, ,
3,,M023.5MM,J2 J4 J6,M023.5MM,SCREWTERMINAL-3.5MM-2,3, ,
4,,M02PTH3,J1 J3 J5,M02PTH3,1X02_LONGPADS,3, ,
5,,M04X2,J7,M04X2,2X4,1, ,
6,,JUMPER-31-2,JP1 JP2,JUMPER-31-2,SJ_3_PASTE1&2,2, ,
7,,LOGO-SFESK,LOGO1 LOGO3,LOGO-SFESK,SFE-LOGO-FLAME,2, ,
8,,OSHW-LOGOS,LOGO2,OSHW-LOGOS,OSHW-LOGO-S,1, ,
9,,0.22OHM1/4W1%(0805),R3,0.22,0805,1, ,
10,,1KOHM1/10W1%(0603),R1 R2,1K,0603-RES,2, ,
11,,10KOHM1/10W1%(0603)0603,R4 R5,10K,0603-RES,2, ,
12,,STAND-OFF,STANDOFF1 STANDOFF2 STANDOFF3,STAND-OFF,STAND-OFF,3, ,
13,,DRV8830,U1,DRV8830,MSOP-10-GNDPAD,1, ,





Project info:
Schematic:,working
Variant:,default
Revision:,
Date:,2023-08-06_12-56-09
KiCad Version:,7.0.6-7.0.6~ubuntu22.04.1
Statistics:
Component Groups:,13
Component Count:,23 (0 SMD/ 0 THT)
Fitted Components:,23 (0 SMD/ 0 THT)
Number of PCBs:,1
Total Components:,23

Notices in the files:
projects/sparkfun_mini_gps_shield/version_current/working/working.kicad_sch:
Released under the Creative Commons
projects/sparkfun_minimoto/version_current/working/working.kicad_sch:
http://creativecommons.org/licenses/by-sa/3.0
parts and their libraries:
Released under the Creative Commons Attribution Share-Alike 4.0 License
